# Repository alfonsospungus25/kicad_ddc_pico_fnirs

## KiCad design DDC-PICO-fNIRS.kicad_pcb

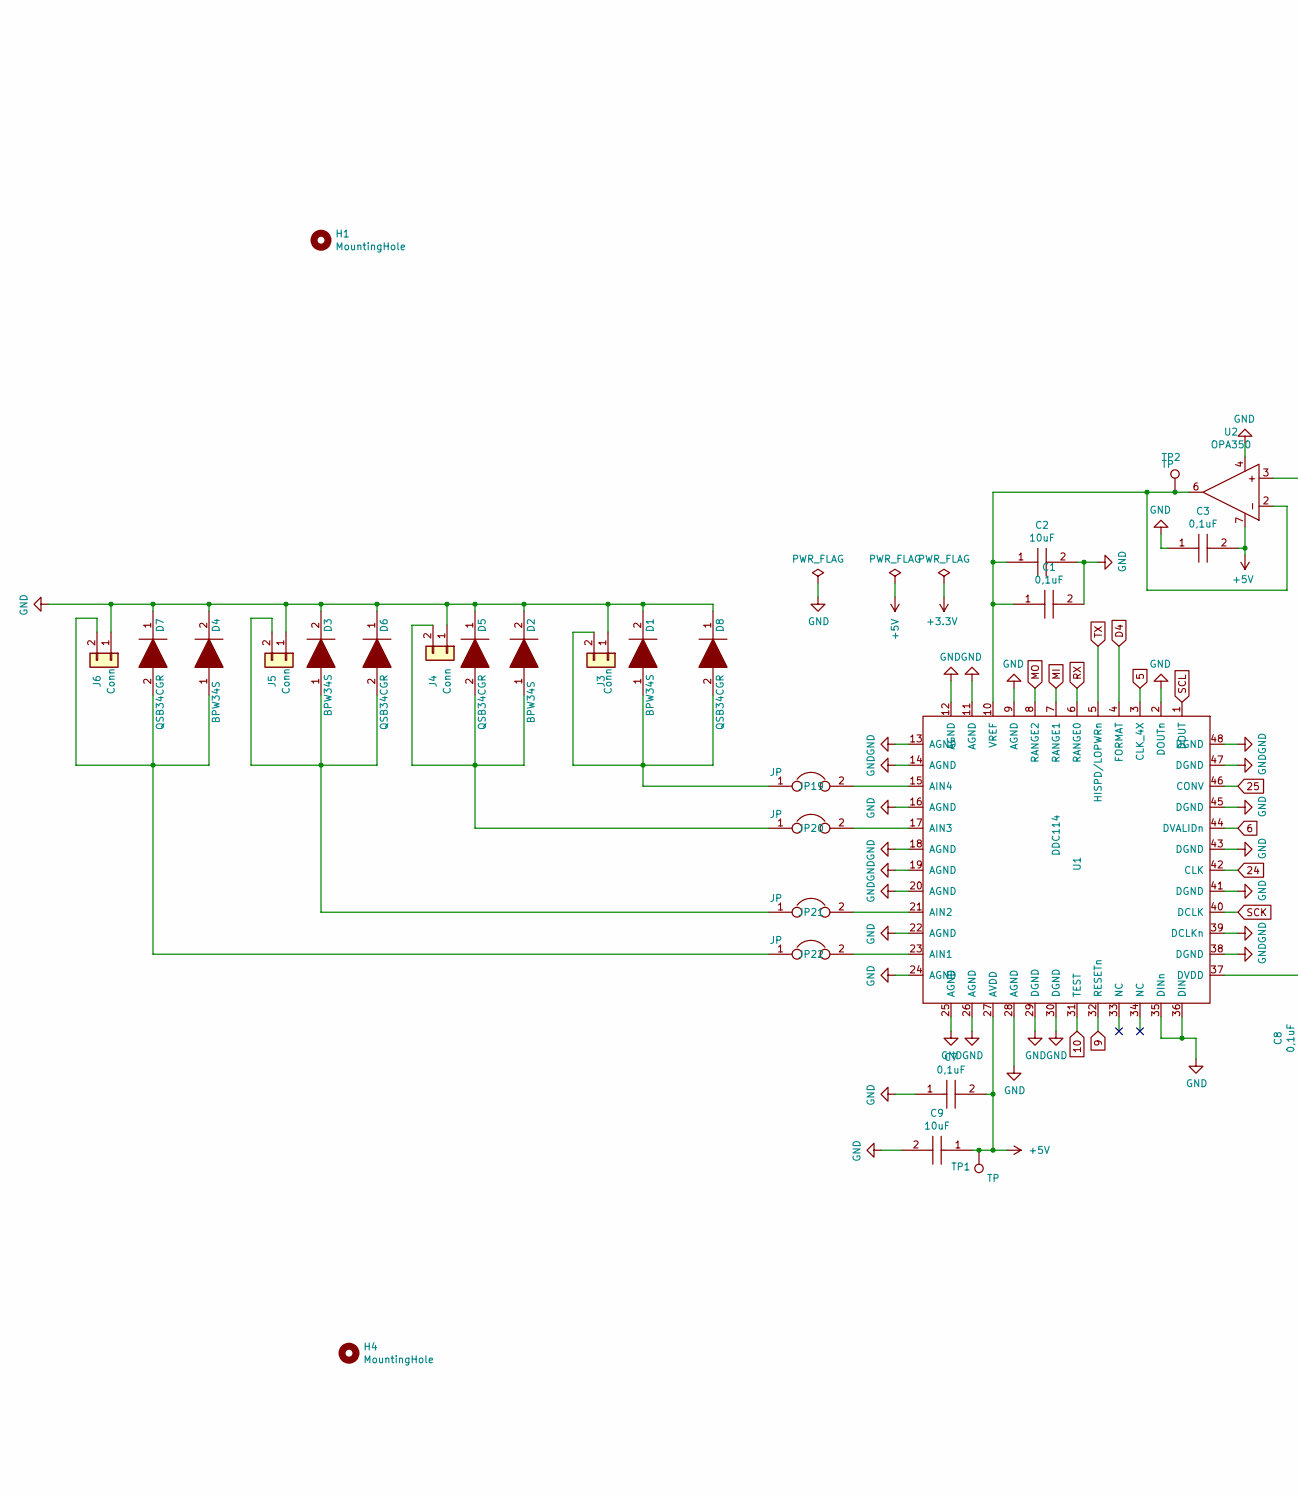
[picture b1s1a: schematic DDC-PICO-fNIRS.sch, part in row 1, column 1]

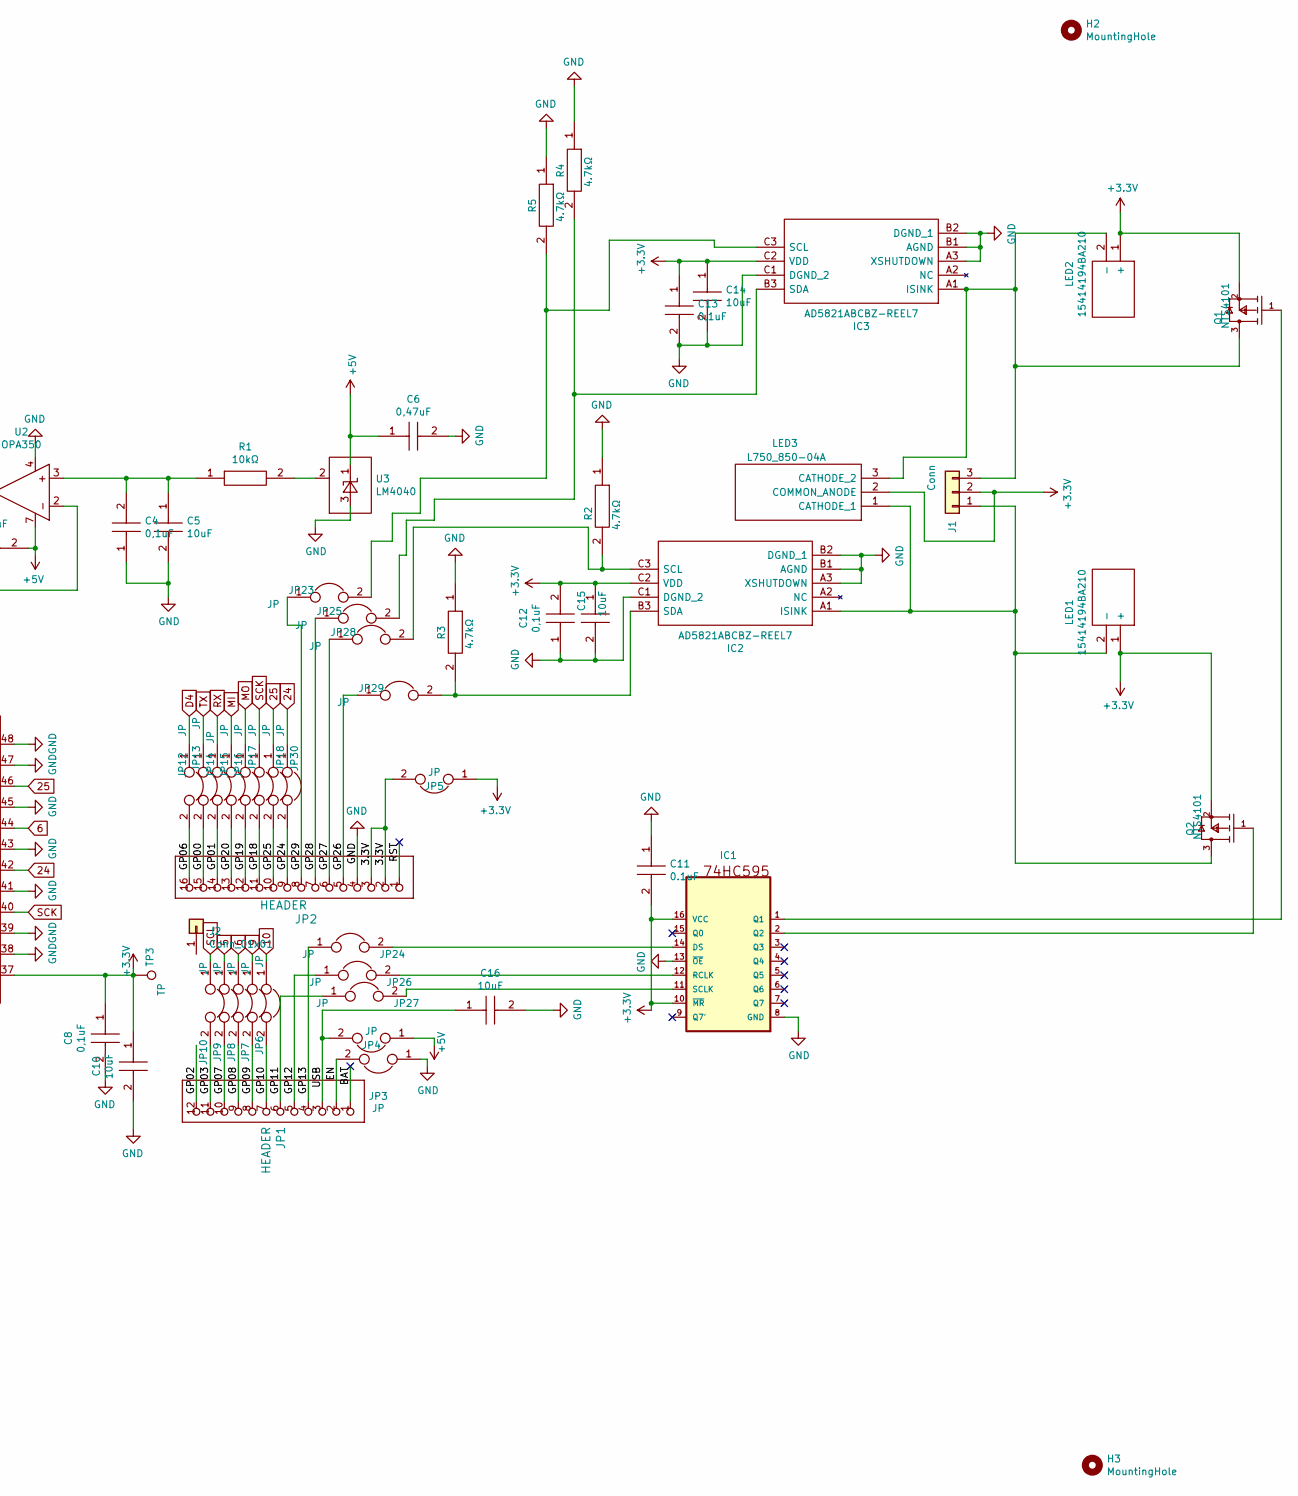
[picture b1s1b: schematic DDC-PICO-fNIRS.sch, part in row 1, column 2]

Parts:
C1, C3, C4, C7, C8, C12, C13: 0,1uF; CC0603KRX7R0BB104; Manufacturer_Part_Number CC0603KRX7R0BB104; Mouser Part Number 603-CC603KRX7R0BB104
C2, C5, C9, C10, C14, C15, C16: 10uF; TPSA106K010R0900; Mouser Part Number 581-TPSA106K010R0900
C6: 0,47uF; C1206C474K5RAC; Manufacturer_Part_Number C1206C474K5RAC; Mouser Part Number 80-C1206C474K5RAC
C11: 0.1uF; CC0603KRX7R0BB104; Manufacturer_Part_Number CC0603KRX7R0BB104; Mouser Part Number 603-CC603KRX7R0BB104
D1, D2, D3, D4: BPW34S; Mouser Part Number 78-BPW34S
D5, D6, D7, D8: QSB34CGR; QSB34CGR_PD_SMD; Mouser Part Number 512-QSB34CGR
H1, H2, H3, H4: MountingHole; MountingHole_2.5mm
IC1: 74HC595; 74HC5955
IC2, IC3: AD5821ABCBZ-REEL7; Manufacturer_Part_Number AD5821ABCBZ-REEL7; Mouser Part Number 584-AD5821ABCBZ-R7
J1: Conn; PinSocket_1x03_P2.54mm_Vertical
J2: Conn_01x01; SolderWire-0.1sqmm_1x01_D0.4mm_OD1mm
J3, J4, J5, J6: Conn; PinSocket_1x02_P2.54mm_Vertical
JP1: HEADER; PinSocket_1x12_P2.54mm_Vertical
JP2: HEADER; PinSocket_1x16_P2.54mm_Vertical
JP3, JP4, JP5, JP6, JP7, JP8, JP9, JP10, JP12, JP13, JP14, JP15, JP16, JP17, JP18, JP19, JP20, JP21, JP22, JP23, JP24, JP25, JP26, JP27, JP28, JP29, JP30: JP; SolderJumper-2_P1.3mm_Open_Pad1.0x1.5mm
LED1, LED2: 15414194BA210; Manufacturer_Part_Number 15414194BA210; Mouser Part Number 710-15414194BA210
LED3: L750_850-04A; L750850-04A_1; Manufacturer_Part_Number L750/850-04A
Q1, Q2: NTS4101; On_Semiconductor-419-04-11_2008-N-MFG; mouser part number 863-NTS4101PT1G; digikey description MOSFET P-CH 20V 1.37A SOT-323
R1: 10kΩ; ERJ-3EKF1002V; Mouser Part Number 667-ERJ-3EKF1002V
R2, R3, R4, R5: 4.7kΩ; CRCW06034K70FKEB; Mouser Part Number 71-CRCW06034K70FKEB
TP1, TP2, TP3: TP; TestPoint_Pad_D2.0mm
U1: DDC114; QFN50P700X700X90-49N
U2: OPA350; OPA350UA
U3: LM4040; LM4040A41IDBZR

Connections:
5: JP9.1, U1.3 (CLK_4X)
6: JP8.1, U1.44 (DVALIDn)
9: JP7.1, U1.32 (RESETn)
10: JP6.1, U1.31 (TEST)
24: JP30.1, U1.42 (CLK)
25: JP18.1, U1.46 (CONV)
+3V3: C8.1, C10.1, C11.2, C12.2, C13.1, C14.1, C15.1, IC1.10 (~MR), IC1.16 (VCC), IC2.C2 (VDD), IC3.C2 (VDD), J1.2, JP5.1, LED1.1 (+), LED2.1 (+), LED3.2 (COMMON_ANODE), Q1.2 (S), Q2.2 (S), TP3.1, U1.37 (DVDD)
+5V: C3.2, C6.1, C7.2, C9.1, JP4.1, TP1.1, U1.27 (AVDD), U2.7, U3.1 (K)
/3.3V: JP2.2, JP2.3, JP5.2
/BAT: JP1.1
/EN: JP1.2, JP3.2
/GP00: JP2.15, JP13.2
/GP01: JP2.14, JP14.2
/GP02: JP1.12
/GP03: JP1.11, JP10.2
/GP06: JP2.16, JP12.2
/GP07: JP1.10, JP9.2
/GP08: JP1.9, JP8.2
/GP09: JP1.8, JP7.2
/GP10: JP1.7, JP6.2
/GP11: JP1.6, JP27.1
/GP12: JP1.5, JP26.1
/GP13: JP1.4, JP24.1
/GP18: JP2.11, JP17.2
/GP19: JP2.12, JP16.2
/GP20: JP2.13, JP15.2
/GP24: JP2.9, JP30.2
/GP25: JP2.10, JP18.2
/GP26: JP2.5, JP29.1
/GP27: JP2.6, JP28.1
/GP28: JP2.7, JP25.1
/GP29: JP2.8, JP23.1
/RST: JP2.1
/USB: C16.1, JP1.3, JP4.2
D4: JP12.1, U1.4 (FORMAT)
GND: C1.2, C2.2, C3.1, C4.1, C5.2, C6.2, C7.1, C8.2, C9.2, C10.2, C11.1, C12.1, C13.2, C14.2, C15.2, C16.2, D1.2, D2.2, D3.2, D4.2, D5.1, D6.1, D7.1, D8.1, IC1.8 (GND), IC1.13 (~OE), IC2.A3 (XSHUTDOWN), IC2.B1 (AGND), IC2.B2 (DGND_1), IC2.C1 (DGND_2), IC3.A3 (XSHUTDOWN), IC3.B1 (AGND), IC3.B2 (DGND_1), IC3.C1 (DGND_2), J3.1, J4.1, J5.1, J6.1, JP2.4, JP3.1, R2.1, R3.1, R4.1, R5.1, U1.2 (DOUTn), U1.9 (AGND), U1.11 (AGND), U1.12 (AGND), U1.13 (AGND), U1.14 (AGND), U1.16 (AGND), U1.18 (AGND), U1.19 (AGND), U1.20 (AGND), U1.22 (AGND), U1.24 (AGND), U1.25 (AGND), U1.26 (AGND), U1.28 (AGND), U1.29 (DGND), U1.30 (DGND), U1.35 (DINn), U1.36 (DIN), U1.38 (DGND), U1.39 (DCLKn), U1.41 (DGND), U1.43 (DGND), U1.45 (DGND), U1.47 (DGND), U1.48 (DGND), U1.49, U2.4, U3.3 (A)
MI: JP15.1, U1.7 (RANGE1)
MO: JP16.1, U1.8 (RANGE2)
unnamed: C1.1, C2.1, TP2.1, U1.10 (VREF), U2.2, U2.6
unnamed: C4.2, C5.1, R1.1, U2.3
unnamed: D1.1, D8.2, J3.2, JP19.1
unnamed: D2.1, D5.2, J4.2, JP20.1
unnamed: D3.1, D6.2, J5.2, JP21.1
unnamed: D4.1, D7.2, J6.2, JP22.1
unnamed: IC1.1 (Q1), Q1.1 (G)
unnamed: IC1.2 (Q2), Q2.1 (G)
unnamed: IC1.11 (SCLK), JP27.2
unnamed: IC1.12 (RCLK), JP26.2
unnamed: IC1.14 (DS), JP24.2
unnamed: IC2.A1 (ISINK), J1.1, LED1.2 (-), LED3.1 (CATHODE_1), Q2.3 (D)
unnamed: IC2.B3 (SDA), JP29.2, R3.2
unnamed: IC2.C3 (SCL), JP28.2, R2.2
unnamed: IC3.A1 (ISINK), J1.3, LED2.2 (-), LED3.3 (CATHODE_2), Q1.3 (D)
unnamed: IC3.B3 (SDA), JP25.2, R4.2
unnamed: IC3.C3 (SCL), JP23.2, R5.2
unnamed: JP19.2, U1.15 (AIN4)
unnamed: JP20.2, U1.17 (AIN3)
unnamed: JP21.2, U1.21 (AIN2)
unnamed: JP22.2, U1.23 (AIN1)
unnamed: R1.2, U3.2
RX: JP14.1, U1.6 (RANGE0)
SCK: JP17.1, U1.40 (DCLK)
SCL: JP10.1, U1.1 (DOUT)
TX: JP13.1, U1.5 (HISPD/LOPWRn)

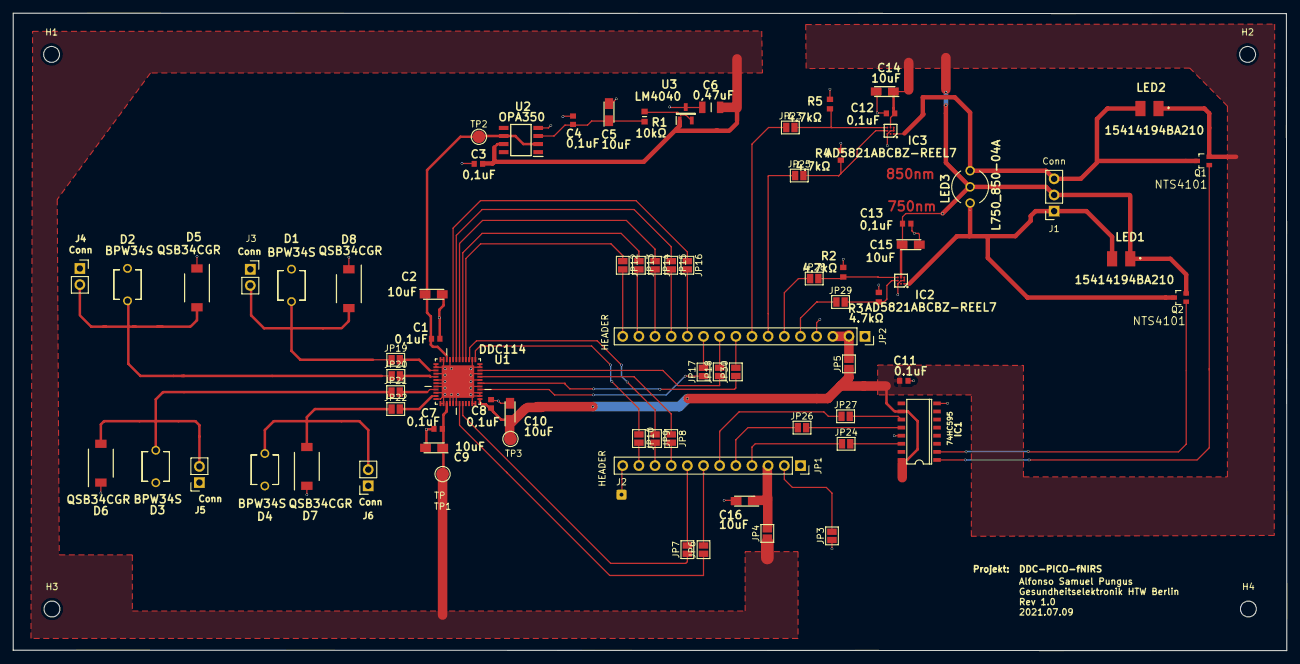
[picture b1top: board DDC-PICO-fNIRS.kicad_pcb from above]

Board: 2 copper layers, 200.2 x 100.2 mm, 82 parts (0 on the bottom side), 61 nets.
